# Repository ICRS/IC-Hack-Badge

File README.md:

# IC-Hack-Badge

Repository for how to use and program the IC Hack PCB badges. They are functionally very similar to the [Raspberry Pi Pico](https://www.raspberrypi.com/products/raspberry-pi-pico/), and any guides for that board will likely work for this one too.

Microcontrollers are small but flexible computers that are great at interacting with the real world. We hope that by giving everyone a powerful microcontroller like the RP2040, they are able to give embedded programming a go and make something cool!

Kits of sensors and electronics are available from ICRS to help build whatever you have in mind. ICRS can also provide knowledge and help with anything relating to hardware projects and the badges.

The badges were designed using [KiCad](https://www.kicad.org/) and all the design files and schematics are available in the [/Hardware](/Hardware/) folder.

## Contents

- [Features](#features)
- [Pinout](#pinout)
- [Writing Code](#writing-code)
- [Uploading Code & Boot Mode](#uploading-code--boot-mode)
- [Resetting Your Badge](#resetting-your-badge)
- [Running From Battery](#running-from-battery)
- [Credits](#credits)

## Features

The features of the board are listed below:

- RP2040: Dual Arm Cortex M0+ cores up to 133MHz
- 264kB RAM
- 2MB Flash
- 24*5 Pixel LED Matrix
- Light up LED logo
- CR2450 Battery holder
- USB C

## Pinout

The functions of each pin are shown here from the back side.

These pins can be connected to using standard Dupont 2.54mm jumper cables.

There are also pins that connect to things internally on the board:

| **Pin Number** | **Function**         |
|----------------|----------------------|
| 0              | Button Y             |
| 1              | Button B             |
| 2              | Button X             |
| 3              | Button A             |
| 4              | Logo H               |
| 5              | Logo C               |
| 6              | Logo I               |
| 15             | Display serial data  |
| 16             | Display enable       |
| 17             | Display serial clock |
| 18             | Display latch        |

## Writing Code

There are several ways of programming the board using either C/C++ or MicroPython.

- [Arduino](#arduino)
- [MicroPython](#micropython)
- [VS Code & C/C++ SDK](#vs-code--cc-sdk)

### Arduino

Arduino is an open source platform for programming microcontrollers in C++. An [Arduino library](https://github.com/ICRS/IC-Hack-Badge-Arduino) has been written for the board that makes using the built in LED matrix easy.

To get started, [download Arduino](https://www.arduino.cc/en/software).

Once you have it running go to `file > preferences` and add the following link to `Additional boards manager URLs`: https://github.com/earlephilhower/arduino-pico/releases/download/global/package_rp2040_index.json

You then need to install support for the RP2040 by going to the board manager tab on the left, searching for "Raspberry Pi Pico" and installing the one by Earle F. Philhower, III.

Go to the board selector in the top, and set the current board to the `Raspberry Pi Pico`.

Finally, we need to install the library made for this board by going to the library manager tab on the left, searching for IC Hack Badge, and installing the most recent version. 

You can then check out example code in `File > Examples > IC Hack Badge`, or start writing your own code.

To program the badge, put the board in [boot mode](#uploading-code--boot-mode) and select the port it is connected to through the same menu where you chose the current board. You may need to check the `Show all ports` box. Then press the upload arrow in the top left.

### MicroPython

To use MicroPython first upload the interpreter to the badge using the [latest firmware from Raspberry Pi](https://micropython.org/download/rp2-pico/rp2-pico-latest.uf2), which you can upload using the instructions in [Uploading Code & Boot Mode](#uploading-code--boot-mode).

You can then connect to the serial port using a program such as PuTTY on Windows, or Minicom on Linux, and start executing code in the MicroPython shell.

Here we are printing "Hello World" over USB, and then setting pin 4 high, which turns on the H LEDs on the badge's logo. The mapping of pins to their functions is shown in the [Pinout](#pinout) section.

You can use the [MicroPico](https://marketplace.visualstudio.com/items?itemName=paulober.pico-w-go) VS Code extension, or [Thonny](https://thonny.org/) to write programs that you can then upload to the badge.

See the [documentation by Raspberry Pi](https://www.raspberrypi.com/documentation/microcontrollers/micropython.html) for more info and APIs.

Currently there is no MicroPython code for writing to the LED matrix, but both the Arduino library and the default firmware have implementations in C++ that could be ported to Python.

### VS Code & C/C++ SDK

The C/C++ SDK is the official way released by Raspberry Pi for programming the RP2040 microcontroller. It offers more depth and features than Arduino, but lacks Arduino's abstractions and libraries, that can make using it harder.

Setting it up can be a bit more challenging than using Arduino too (especially on Windows), and we recommend following [Raspberry Pi's guides](https://www.raspberrypi.com/documentation/microcontrollers/c_sdk.html) if you want to do so.

The firmware flashed to all the badges was written using the C/C++ SDK, and can be found in the [/SDK](/SDK/) folder for reference. Sorry for the spaghetti, blame Haotian -_-

## Uploading Code & Boot Mode

Plug the board into a computer using the USB C connector. Then in order to program the board it needs to be put into "boot mode". This is done by **holding down** both the reset button (**RST**) on the top of the board **and** the boot button (**BOOT**) on the bottom of the board. Then **release RST**, wait a bit and **release BOOT**.

This will make the board show up as a USB drive that you can drag and drop compiled uf2 binaries into.

## Resetting Your Badge
The default firmware is [firmware.uf2](/firmware.uf2) and you can upload it to your badge with a USB C cable after putting it in [boot mode](#uploading-code--boot-mode).

## Running From Battery

Coin cells are able to supply a maximum of around 10mA continuously (ideally <2mA), but the RP2040 when running at full speed can draw well over 20mA. This means that the power consumption needs to be lowered by changing the CPU frequency and voltage so it can be run on the battery.

This can be done in C/C++ using the following lines:

```C
#include "pico/stdlib.h"
#include "hardware/vreg.h"

void main() {
  vreg_set_voltage(VREG_VOLTAGE_0_90);
  set_sys_clock_khz(18000, false);
  ...
}
```

This lowers the core voltage to 0.9V, and the core frequency to 18MHz which draws around 6mA. This was found to be a good balance of low power and stablility, however it means the USB is disabled since it requires a minimum of 48MHz.

> [!NOTE]
> The battery should last for well over 24 hours with the default firmware, so it can be left on for the whole hackathon.

Using the pico extras repo in the C/C++ SDK (sadly not in Arduino) the chip can be put to sleep which only draws 0.7mA. You can find out more about pico_sleep [here](https://github.com/raspberrypi/pico-extras/tree/master).

When running MicroPython the RP2040 consumes too much power for the battery, so you should use USB instead.

## Credits

Hardware: Ben Smith

Artwork: Anna Votin and Kevin Wang

Firmware: Haotian Wu (+ Ben Smith)

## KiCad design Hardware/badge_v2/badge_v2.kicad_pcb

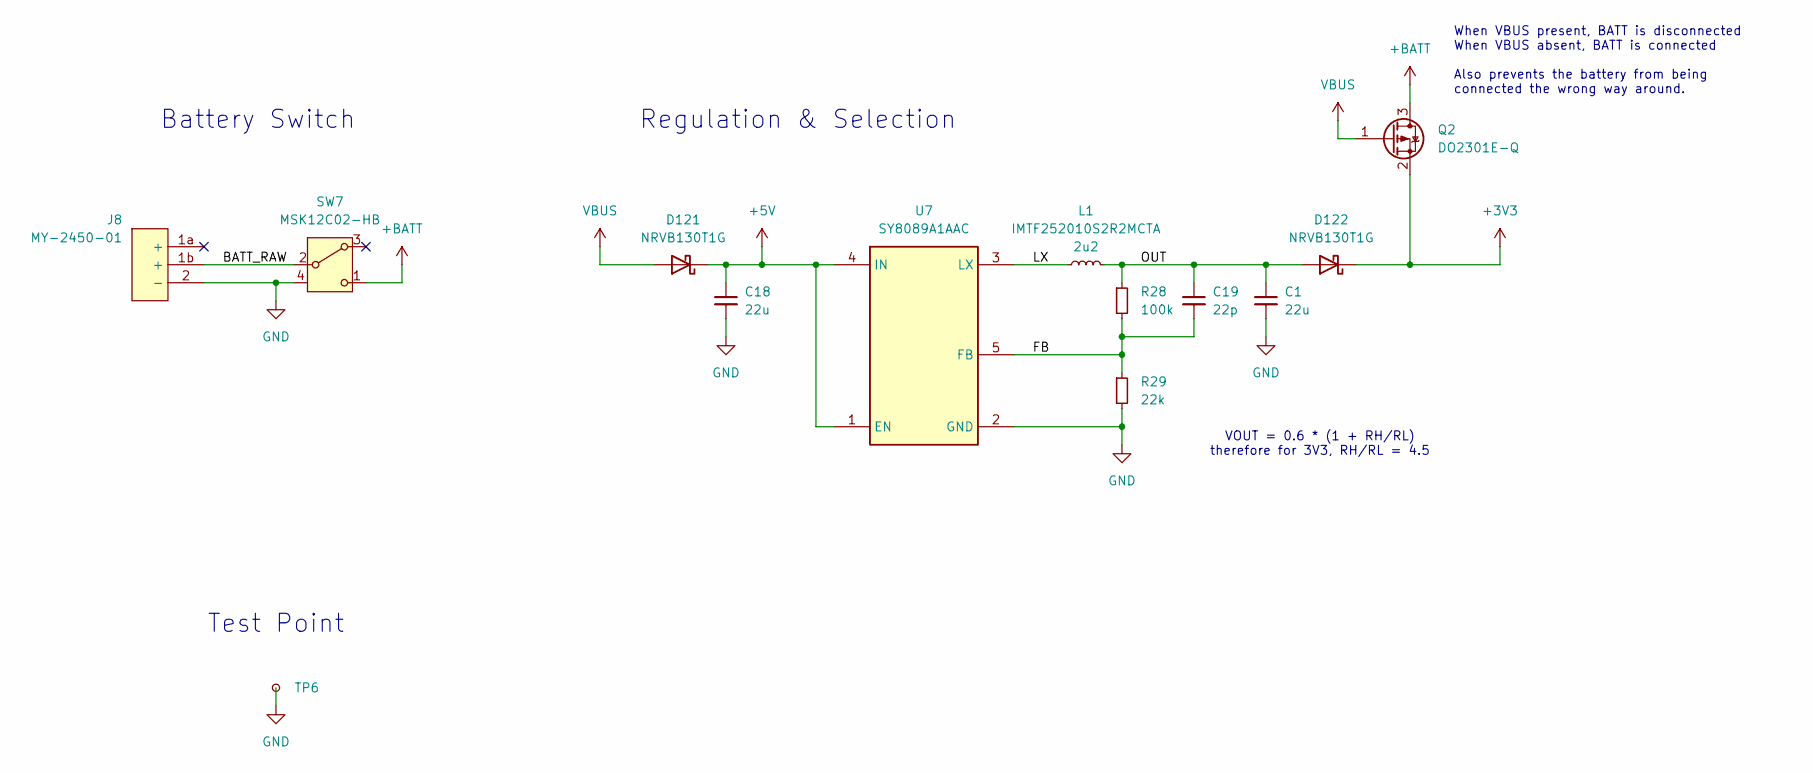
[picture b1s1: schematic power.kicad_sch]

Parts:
C1, C18: 22u; C_0603_1608Metric
C19: 22p; C_0402_1005Metric
D121, D122: NRVB130T1G; D_SOD-123F; LCSC part number C917121
J8: MY-2450-01; LCSC part number C964845
L1: 2u2; L_1008_2520Metric; Part IMTF252010S2R2MCTA; LCSC part number C19631588
Q2: DO2301E-Q; SOT-23; LCSC part number C41384537
R28: 100k; R_0402_1005Metric
R29: 22k; R_0402_1005Metric
SW7: MSK12C02-HB; LCSC part number C5149817
TP6: TestPoint_Small; TestPoint_Pad_D3.0mm
U7: SY8089A1AAC; SOT95P285X130-5N; Manufacturer_Part_Number SY8089A1AAC; LCSC part number C479074

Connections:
+3V3: D122.1 (K), Q2.2 (S); also elsewhere on the board
+5V: C18.1, D121.1 (K), U7.1 (EN), U7.4 (IN); also elsewhere on the board
+BATT: Q2.3 (D), SW7.1 (C)
/Power/BATT_RAW: J8.1b (+), SW7.2 (B)
/Power/FB: C19.2, R28.2, R29.1, U7.5 (FB)
/Power/LX: L1.1, U7.3 (LX)
/Power/OUT: C1.1, C19.1, D122.2 (A), L1.2, R28.1
GND: C1.2, C18.2, J8.2 (-), R29.2, SW7.4, TP6.1, U7.2 (GND); also elsewhere on the board
VBUS: D121.2 (A), Q2.1 (G); also elsewhere on the board

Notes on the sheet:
Battery Switch
Test Point
When VBUS present, BATT is disconnected When VBUS absent, BATT is connected Also prevents the battery from being connected the wrong way around.
Regulation & Selection
VOUT = 0.6 * (1 + RH/RL) therefore for 3V3, RH/RL = 4.5

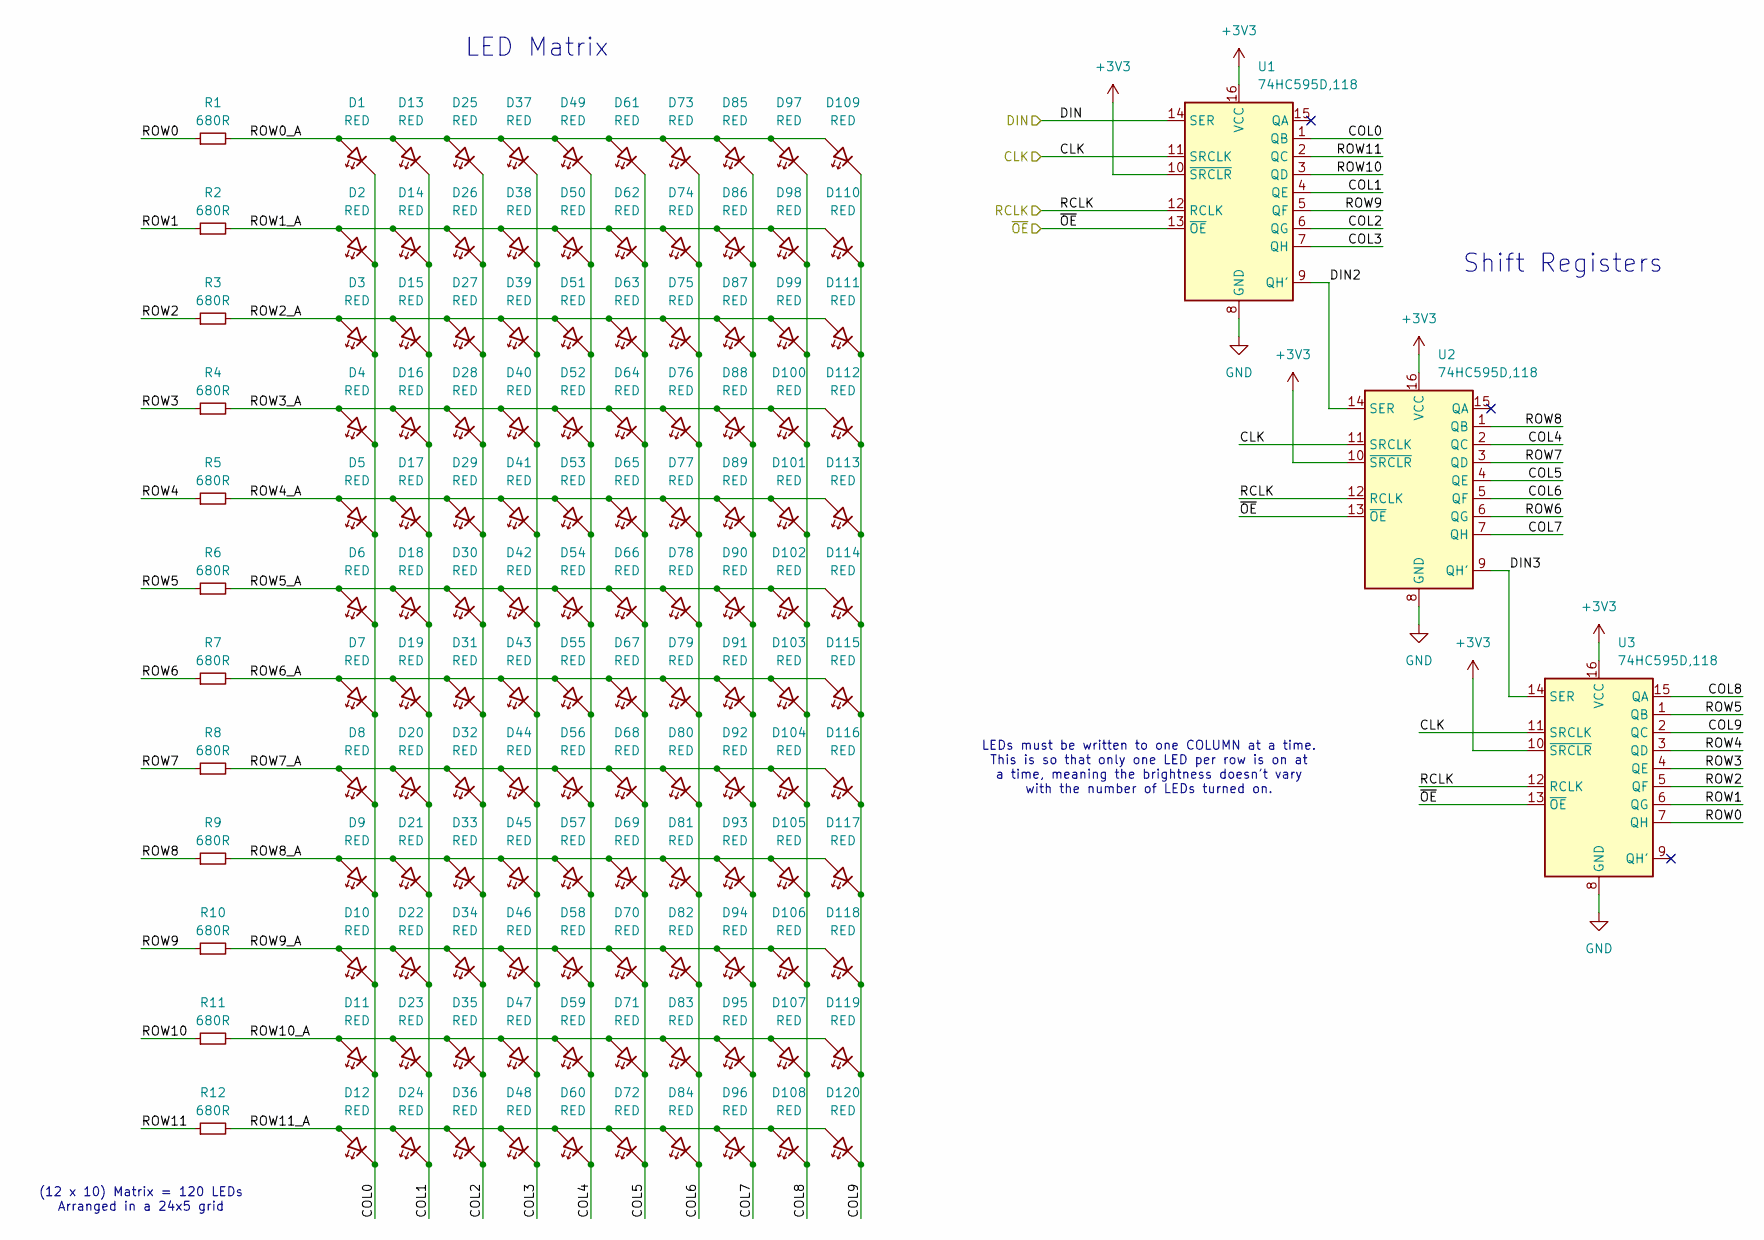
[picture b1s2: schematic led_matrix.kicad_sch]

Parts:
D1, D2, D3, D4, D5, D6, D7, D8, D9, D10, D11, D12, D13, D14, D15, D16, D17, D18, D19, D20, D21, D22, D23, D24, D25, D26, D27, D28, D29, D30, D31, D32, D33, D34, D35, D36, D37, D38, D39, D40, D41, D42, D43, D44, D45, D46, D47, D48, D49, D50, D51, D52, D53, D54, D55, D56, D57, D58, D59, D60, D61, D62, D63, D64, D65, D66, D67, D68, D69, D70, D71, D72, D73, D74, D75, D76, D77, D78, D79, D80, D81, D82, D83, D84, D85, D86, D87, D88, D89, D90, D91, D92, D93, D94, D95, D96, D97, D98, D99, D100, D101, D102, D103, D104, D105, D106, D107, D108, D109, D110, D111, D112, D113, D114, D115, D116, D117, D118, D119, D120: RED; LED_0402_1005Metric
R1, R2, R3, R4, R5, R6, R7, R8, R9, R10, R11, R12: 680R; R_0402_1005Metric
U1, U2, U3: 74HC595D,118; SOIC-16_3.9x9.9mm_P1.27mm; LCSC part number C5947

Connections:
+3V3: U1.10 (~SRCLR), U1.16 (VCC), U2.10 (~SRCLR), U2.16 (VCC), U3.10 (~SRCLR), U3.16 (VCC); also elsewhere on the board
/LED Matrix/CLK: U1.11 (SRCLK), U2.11 (SRCLK), U3.11 (SRCLK); also elsewhere on the board
/LED Matrix/COL0: D1.1 (K), D2.1 (K), D3.1 (K), D4.1 (K), D5.1 (K), D6.1 (K), D7.1 (K), D8.1 (K), D9.1 (K), D10.1 (K), D11.1 (K), D12.1 (K), U1.1 (QB)
/LED Matrix/COL1: D13.1 (K), D14.1 (K), D15.1 (K), D16.1 (K), D17.1 (K), D18.1 (K), D19.1 (K), D20.1 (K), D21.1 (K), D22.1 (K), D23.1 (K), D24.1 (K), U1.4 (QE)
/LED Matrix/COL2: D25.1 (K), D26.1 (K), D27.1 (K), D28.1 (K), D29.1 (K), D30.1 (K), D31.1 (K), D32.1 (K), D33.1 (K), D34.1 (K), D35.1 (K), D36.1 (K), U1.6 (QG)
/LED Matrix/COL3: D37.1 (K), D38.1 (K), D39.1 (K), D40.1 (K), D41.1 (K), D42.1 (K), D43.1 (K), D44.1 (K), D45.1 (K), D46.1 (K), D47.1 (K), D48.1 (K), U1.7 (QH)
/LED Matrix/COL4: D49.1 (K), D50.1 (K), D51.1 (K), D52.1 (K), D53.1 (K), D54.1 (K), D55.1 (K), D56.1 (K), D57.1 (K), D58.1 (K), D59.1 (K), D60.1 (K), U2.2 (QC)
/LED Matrix/COL5: D61.1 (K), D62.1 (K), D63.1 (K), D64.1 (K), D65.1 (K), D66.1 (K), D67.1 (K), D68.1 (K), D69.1 (K), D70.1 (K), D71.1 (K), D72.1 (K), U2.4 (QE)
/LED Matrix/COL6: D73.1 (K), D74.1 (K), D75.1 (K), D76.1 (K), D77.1 (K), D78.1 (K), D79.1 (K), D80.1 (K), D81.1 (K), D82.1 (K), D83.1 (K), D84.1 (K), U2.5 (QF)
/LED Matrix/COL7: D85.1 (K), D86.1 (K), D87.1 (K), D88.1 (K), D89.1 (K), D90.1 (K), D91.1 (K), D92.1 (K), D93.1 (K), D94.1 (K), D95.1 (K), D96.1 (K), U2.7 (QH)
/LED Matrix/COL8: D97.1 (K), D98.1 (K), D99.1 (K), D100.1 (K), D101.1 (K), D102.1 (K), D103.1 (K), D104.1 (K), D105.1 (K), D106.1 (K), D107.1 (K), D108.1 (K), U3.15 (QA)
/LED Matrix/COL9: D109.1 (K), D110.1 (K), D111.1 (K), D112.1 (K), D113.1 (K), D114.1 (K), D115.1 (K), D116.1 (K), D117.1 (K), D118.1 (K), D119.1 (K), D120.1 (K), U3.2 (QC)
/LED Matrix/DIN: U1.14 (SER); also elsewhere on the board
/LED Matrix/DIN2: U1.9 (QH'), U2.14 (SER)
/LED Matrix/DIN3: U2.9 (QH'), U3.14 (SER)
/LED Matrix/RCLK: U1.12 (RCLK), U2.12 (RCLK), U3.12 (RCLK); also elsewhere on the board
/LED Matrix/ROW0: R1.1, U3.7 (QH)
/LED Matrix/ROW0_A: D1.2 (A), D13.2 (A), D25.2 (A), D37.2 (A), D49.2 (A), D61.2 (A), D73.2 (A), D85.2 (A), D97.2 (A), D109.2 (A), R1.2
/LED Matrix/ROW1: R2.1, U3.6 (QG)
/LED Matrix/ROW1_A: D2.2 (A), D14.2 (A), D26.2 (A), D38.2 (A), D50.2 (A), D62.2 (A), D74.2 (A), D86.2 (A), D98.2 (A), D110.2 (A), R2.2
/LED Matrix/ROW2: R3.1, U3.5 (QF)
/LED Matrix/ROW2_A: D3.2 (A), D15.2 (A), D27.2 (A), D39.2 (A), D51.2 (A), D63.2 (A), D75.2 (A), D87.2 (A), D99.2 (A), D111.2 (A), R3.2
/LED Matrix/ROW3: R4.1, U3.4 (QE)
/LED Matrix/ROW3_A: D4.2 (A), D16.2 (A), D28.2 (A), D40.2 (A), D52.2 (A), D64.2 (A), D76.2 (A), D88.2 (A), D100.2 (A), D112.2 (A), R4.2
/LED Matrix/ROW4: R5.1, U3.3 (QD)
/LED Matrix/ROW4_A: D5.2 (A), D17.2 (A), D29.2 (A), D41.2 (A), D53.2 (A), D65.2 (A), D77.2 (A), D89.2 (A), D101.2 (A), D113.2 (A), R5.2
/LED Matrix/ROW5: R6.1, U3.1 (QB)
/LED Matrix/ROW5_A: D6.2 (A), D18.2 (A), D30.2 (A), D42.2 (A), D54.2 (A), D66.2 (A), D78.2 (A), D90.2 (A), D102.2 (A), D114.2 (A), R6.2
/LED Matrix/ROW6: R7.1, U2.6 (QG)
/LED Matrix/ROW6_A: D7.2 (A), D19.2 (A), D31.2 (A), D43.2 (A), D55.2 (A), D67.2 (A), D79.2 (A), D91.2 (A), D103.2 (A), D115.2 (A), R7.2
/LED Matrix/ROW7: R8.1, U2.3 (QD)
/LED Matrix/ROW7_A: D8.2 (A), D20.2 (A), D32.2 (A), D44.2 (A), D56.2 (A), D68.2 (A), D80.2 (A), D92.2 (A), D104.2 (A), D116.2 (A), R8.2
/LED Matrix/ROW8: R9.1, U2.1 (QB)
/LED Matrix/ROW8_A: D9.2 (A), D21.2 (A), D33.2 (A), D45.2 (A), D57.2 (A), D69.2 (A), D81.2 (A), D93.2 (A), D105.2 (A), D117.2 (A), R9.2
/LED Matrix/ROW9: R10.1, U1.5 (QF)
/LED Matrix/ROW9_A: D10.2 (A), D22.2 (A), D34.2 (A), D46.2 (A), D58.2 (A), D70.2 (A), D82.2 (A), D94.2 (A), D106.2 (A), D118.2 (A), R10.2
/LED Matrix/ROW10: R11.1, U1.3 (QD)
/LED Matrix/ROW10_A: D11.2 (A), D23.2 (A), D35.2 (A), D47.2 (A), D59.2 (A), D71.2 (A), D83.2 (A), D95.2 (A), D107.2 (A), D119.2 (A), R11.2
/LED Matrix/ROW11: R12.1, U1.2 (QC)
/LED Matrix/ROW11_A: D12.2 (A), D24.2 (A), D36.2 (A), D48.2 (A), D60.2 (A), D72.2 (A), D84.2 (A), D96.2 (A), D108.2 (A), D120.2 (A), R12.2
/LED Matrix/~OE: U1.13 (~OE), U2.13 (~OE), U3.13 (~OE); also elsewhere on the board
GND: U1.8 (GND), U2.8 (GND), U3.8 (GND); also elsewhere on the board

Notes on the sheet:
LEDs must be written to one COLUMN at a time. This is so that only one LED per row is on at a time, meaning the brightness doesn't vary with the number of LEDs turned on.
LED Matrix
Shift Registers
(12 x 10) Matrix = 120 LEDs Arranged in a 24x5 grid

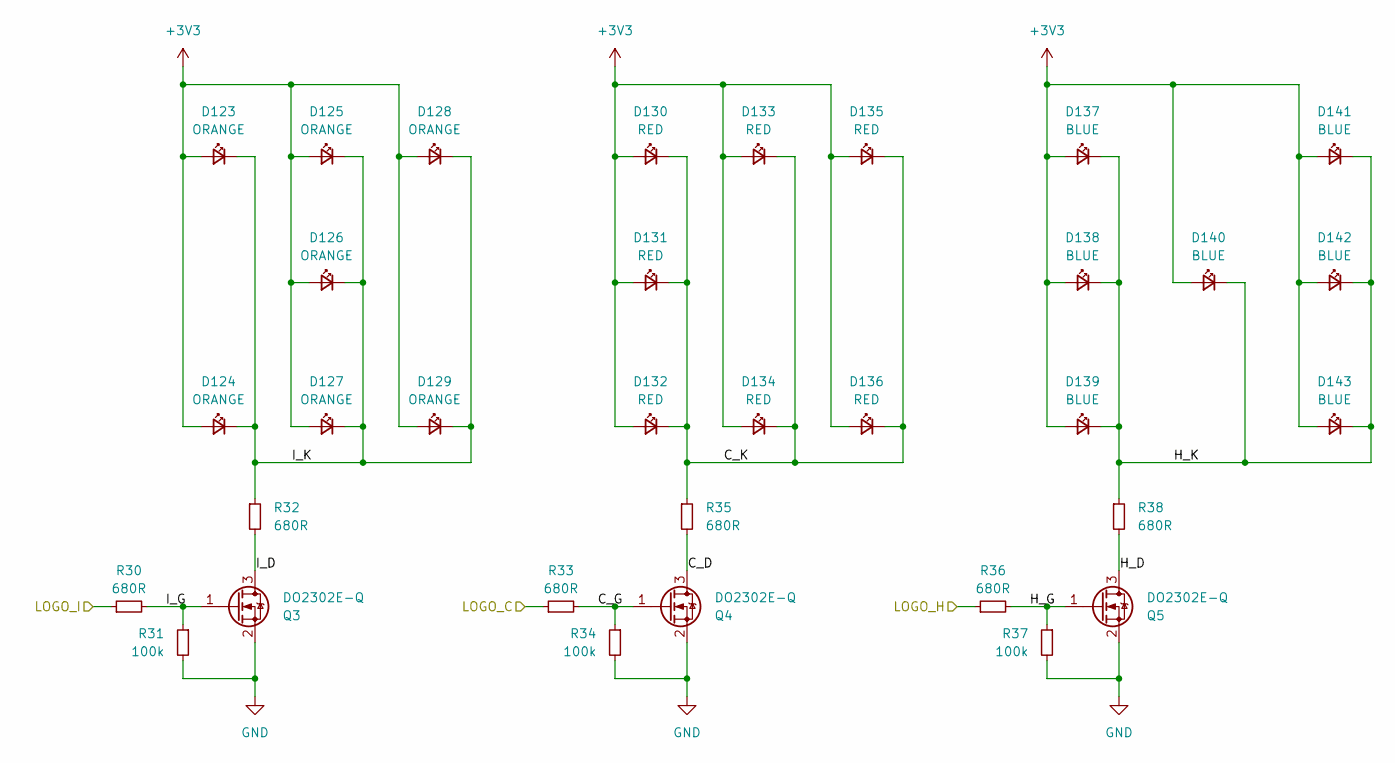
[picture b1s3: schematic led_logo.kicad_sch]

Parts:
D123, D124, D125, D126, D127, D128, D129: ORANGE; LED_0402_1005Metric
D130, D131, D132, D133, D134, D135, D136: RED; LED_0402_1005Metric
D137, D138, D139, D140, D141, D142, D143: BLUE; LED_0402_1005Metric
Q3, Q4, Q5: DO2302E-Q; SOT-23; LCSC part number C41384540
R30, R32, R33, R35, R36, R38: 680R; R_0402_1005Metric
R31, R34, R37: 100k; R_0402_1005Metric

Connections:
+3V3: D123.2 (A), D124.2 (A), D125.2 (A), D126.2 (A), D127.2 (A), D128.2 (A), D129.2 (A), D130.2 (A), D131.2 (A), D132.2 (A), D133.2 (A), D134.2 (A), D135.2 (A), D136.2 (A), D137.2 (A), D138.2 (A), D139.2 (A), D140.2 (A), D141.2 (A), D142.2 (A), D143.2 (A); also elsewhere on the board
/LED Logo/C_D: Q4.3 (D), R35.2
/LED Logo/C_G: Q4.1 (G), R33.2, R34.1
/LED Logo/C_K: D130.1 (K), D131.1 (K), D132.1 (K), D133.1 (K), D134.1 (K), D135.1 (K), D136.1 (K), R35.1
/LED Logo/H_D: Q5.3 (D), R38.2
/LED Logo/H_G: Q5.1 (G), R36.2, R37.1
/LED Logo/H_K: D137.1 (K), D138.1 (K), D139.1 (K), D140.1 (K), D141.1 (K), D142.1 (K), D143.1 (K), R38.1
/LED Logo/I_D: Q3.3 (D), R32.2
/LED Logo/I_G: Q3.1 (G), R30.2, R31.1
/LED Logo/I_K: D123.1 (K), D124.1 (K), D125.1 (K), D126.1 (K), D127.1 (K), D128.1 (K), D129.1 (K), R32.1
/LED Logo/LOGO_C: R33.1; also elsewhere on the board
/LED Logo/LOGO_H: R36.1; also elsewhere on the board
/LED Logo/LOGO_I: R30.1; also elsewhere on the board
GND: Q3.2 (S), Q4.2 (S), Q5.2 (S), R31.2, R34.2, R37.2; also elsewhere on the board

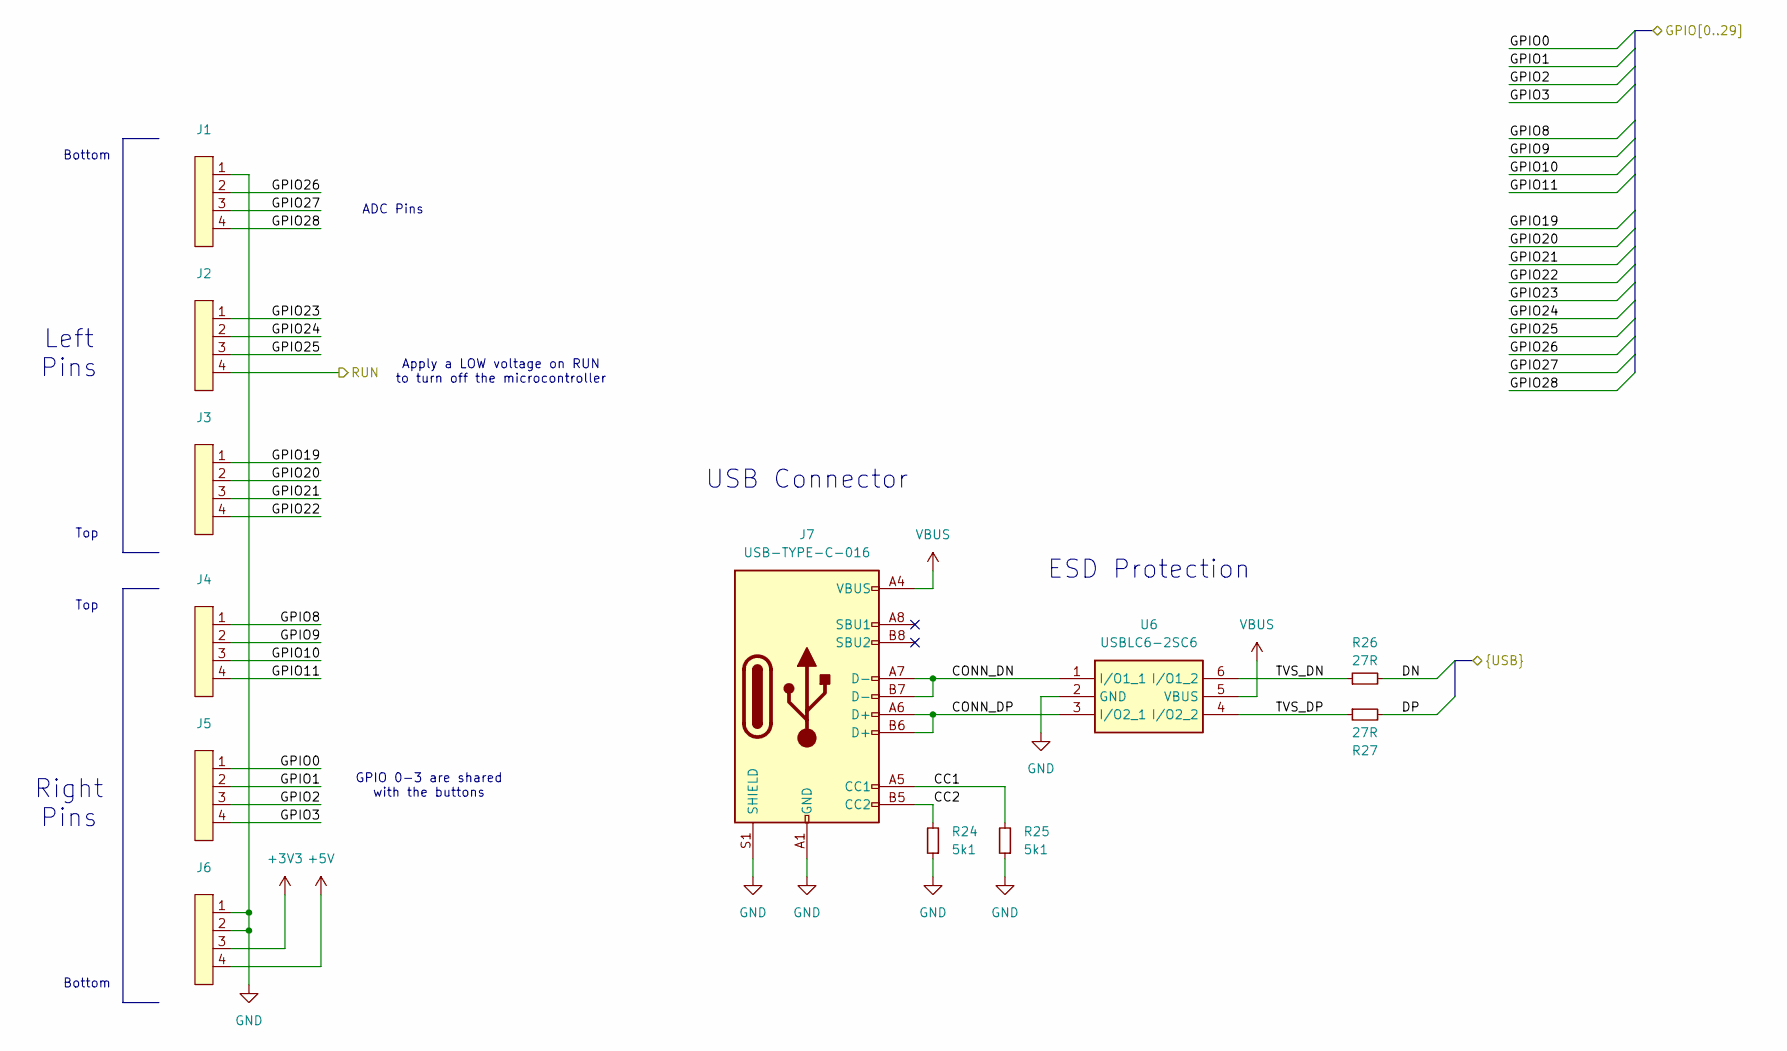
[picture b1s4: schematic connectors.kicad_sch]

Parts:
J1, J2, J3, J4, J5, J6: X6511FRS-04-C85D30; LCSC part number C5142237
J7: USB-TYPE-C-016; LCSC part number C2927036
R24, R25: 5k1; R_0402_1005Metric
R26, R27: 27R; R_0402_1005Metric
U6: USBLC6-2SC6; SOT95P280X145-6N; Manufacturer_Part_Number USBLC6-2SC6; Mouser Part Number 511-USBLC6-2SC6

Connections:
+3V3: J6.3; also elsewhere on the board
+5V: J6.4; also elsewhere on the board
/Connectors/CC1: J7.A5 (CC1), R25.2
/Connectors/CC2: J7.B5 (CC2), R24.2
/Connectors/CONN_DN: J7.A7 (D-), J7.B7 (D-), U6.1 (I/O1_1)
/Connectors/CONN_DP: J7.A6 (D+), J7.B6 (D+), U6.3 (I/O2_1)
/Connectors/DN: R26.2; also elsewhere on the board
/Connectors/DP: R27.2; also elsewhere on the board
/Connectors/GPIO0: J5.1; also elsewhere on the board
/Connectors/GPIO1: J5.2; also elsewhere on the board
/Connectors/GPIO2: J5.3; also elsewhere on the board
/Connectors/GPIO3: J5.4; also elsewhere on the board
/Connectors/GPIO8: J4.1; also elsewhere on the board
/Connectors/GPIO9: J4.2; also elsewhere on the board
/Connectors/GPIO10: J4.3; also elsewhere on the board
/Connectors/GPIO11: J4.4; also elsewhere on the board
/Connectors/GPIO19: J3.1; also elsewhere on the board
/Connectors/GPIO20: J3.2; also elsewhere on the board
/Connectors/GPIO21: J3.3; also elsewhere on the board
/Connectors/GPIO22: J3.4; also elsewhere on the board
/Connectors/GPIO23: J2.1; also elsewhere on the board
/Connectors/GPIO24: J2.2; also elsewhere on the board
/Connectors/GPIO25: J2.3; also elsewhere on the board
/Connectors/GPIO26: J1.2; also elsewhere on the board
/Connectors/GPIO27: J1.3; also elsewhere on the board
/Connectors/GPIO28: J1.4; also elsewhere on the board
/Connectors/TVS_DN: R26.1, U6.6 (I/O1_2)
/Connectors/TVS_DP: R27.1, U6.4 (I/O2_2)
/RP2040/RUN: J2.4; also elsewhere on the board
GND: J1.1, J6.1, J6.2, J7.A1 (GND), J7.A12 (GND), J7.B1 (GND), J7.B12 (GND), J7.S1 (SHIELD), R24.1, R25.1, U6.2 (GND); also elsewhere on the board
VBUS: J7.A4 (VBUS), J7.A9 (VBUS), J7.B4 (VBUS), J7.B9 (VBUS), U6.5 (VBUS); also elsewhere on the board

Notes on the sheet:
ESD Protection
ADC Pins
Top
GPIO 0-3 are shared with the buttons
Left Pins
Apply a LOW voltage on RUN to turn off the microcontroller
USB Connector
Bottom
Right Pins

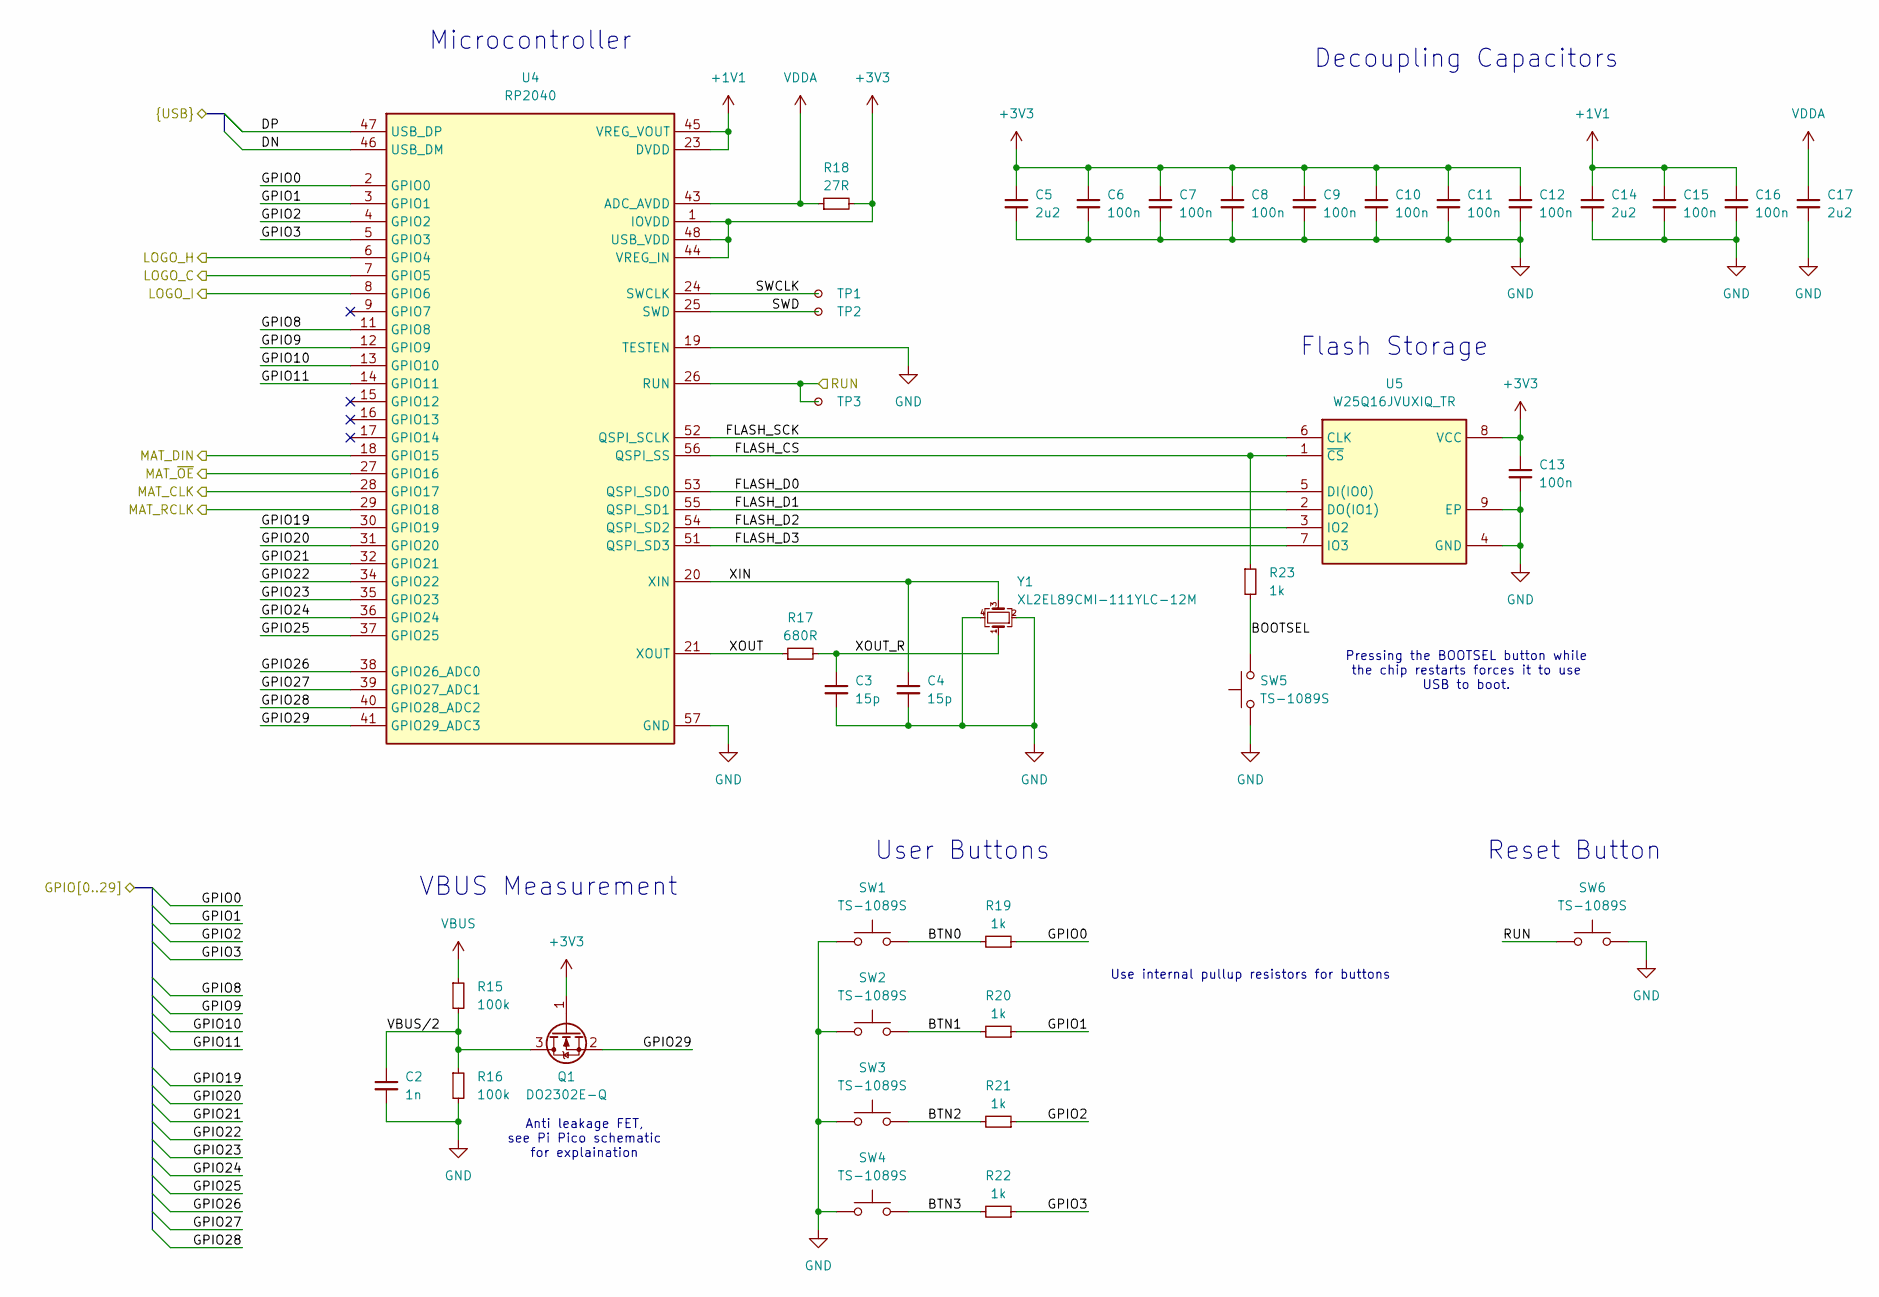
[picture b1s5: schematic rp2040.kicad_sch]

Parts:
C2: 1n; C_0402_1005Metric
C3, C4: 15p; C_0402_1005Metric
C5, C14, C17: 2u2; C_0402_1005Metric
C6, C7, C8, C9, C10, C11, C12, C13, C15, C16: 100n; C_0402_1005Metric
Q1: DO2302E-Q; SOT-23; LCSC part number C41384540
R15, R16: 100k; R_0402_1005Metric
R17: 680R; R_0402_1005Metric
R18: 27R; R_0402_1005Metric
R19, R20, R21, R22, R23: 1k; R_0402_1005Metric
SW1, SW2, SW3, SW4, SW5, SW6: TS-1089S; LCSC part number C455282
TP1, TP2, TP3: TestPoint_Small; TestPoint_Pad_D3.0mm
U4: RP2040; QFN-56-1EP_7x7mm_P0.4mm_EP3.2x3.2mm; LCSC part number C2040
U5: W25Q16JVUXIQ_TR; SON50P300X200X60-9N; Manufacturer_Part_Number W25Q16JVUXIQ TR; Mouser Part Number 454-W25Q16JVUXIQTR
Y1: XL2EL89CMI-111YLC-12M; Crystal_SMD_3225-4Pin_3.2x2.5mm; LCSC part number C7500570

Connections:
+1V1: C14.1, C15.1, C16.1, U4.23 (DVDD), U4.45 (VREG_VOUT), U4.50 (DVDD)
+3V3: C5.1, C6.1, C7.1, C8.1, C9.1, C10.1, C11.1, C12.1, C13.1, Q1.1 (G), R18.2, U4.1 (IOVDD), U4.10 (IOVDD), U4.22 (IOVDD), U4.33 (IOVDD), U4.42 (IOVDD), U4.44 (VREG_IN), U4.48 (USB_VDD), U4.49 (IOVDD), U5.8 (VCC); also elsewhere on the board
/Connectors/DN: U4.46 (USB_DM); also elsewhere on the board
/Connectors/DP: U4.47 (USB_DP); also elsewhere on the board
/Connectors/GPIO0: R19.1, U4.2 (GPIO0); also elsewhere on the board
/Connectors/GPIO1: R20.1, U4.3 (GPIO1); also elsewhere on the board
/Connectors/GPIO2: R21.1, U4.4 (GPIO2); also elsewhere on the board
/Connectors/GPIO3: R22.1, U4.5 (GPIO3); also elsewhere on the board
/Connectors/GPIO8: U4.11 (GPIO8); also elsewhere on the board
/Connectors/GPIO9: U4.12 (GPIO9); also elsewhere on the board
/Connectors/GPIO10: U4.13 (GPIO10); also elsewhere on the board
/Connectors/GPIO11: U4.14 (GPIO11); also elsewhere on the board
/Connectors/GPIO19: U4.30 (GPIO19); also elsewhere on the board
/Connectors/GPIO20: U4.31 (GPIO20); also elsewhere on the board
/Connectors/GPIO21: U4.32 (GPIO21); also elsewhere on the board
/Connectors/GPIO22: U4.34 (GPIO22); also elsewhere on the board
/Connectors/GPIO23: U4.35 (GPIO23); also elsewhere on the board
/Connectors/GPIO24: U4.36 (GPIO24); also elsewhere on the board
/Connectors/GPIO25: U4.37 (GPIO25); also elsewhere on the board
/Connectors/GPIO26: U4.38 (GPIO26_ADC0); also elsewhere on the board
/Connectors/GPIO27: U4.39 (GPIO27_ADC1); also elsewhere on the board
/Connectors/GPIO28: U4.40 (GPIO28_ADC2); also elsewhere on the board
/Connectors/GPIO29: Q1.2 (S), U4.41 (GPIO29_ADC3)
/LED Logo/LOGO_C: U4.7 (GPIO5); also elsewhere on the board
/LED Logo/LOGO_H: U4.6 (GPIO4); also elsewhere on the board
/LED Logo/LOGO_I: U4.8 (GPIO6); also elsewhere on the board
/LED Matrix/CLK: U4.28 (GPIO17); also elsewhere on the board
/LED Matrix/DIN: U4.18 (GPIO15); also elsewhere on the board
/LED Matrix/RCLK: U4.29 (GPIO18); also elsewhere on the board
/LED Matrix/~OE: U4.27 (GPIO16); also elsewhere on the board
/RP2040/BOOTSEL: R23.2, SW5.2
/RP2040/BTN0: R19.2, SW1.1
/RP2040/BTN1: R20.2, SW2.1
/RP2040/BTN2: R21.2, SW3.1
/RP2040/BTN3: R22.2, SW4.1
/RP2040/FLASH_CS: R23.1, U4.56 (QSPI_SS), U5.1 (~CS)
/RP2040/FLASH_D0: U4.53 (QSPI_SD0), U5.5 (DI(IO0))
/RP2040/FLASH_D1: U4.55 (QSPI_SD1), U5.2 (DO(IO1))
/RP2040/FLASH_D2: U4.54 (QSPI_SD2), U5.3 (IO2)
/RP2040/FLASH_D3: U4.51 (QSPI_SD3), U5.7 (IO3)
/RP2040/FLASH_SCK: U4.52 (QSPI_SCLK), U5.6 (CLK)
/RP2040/RUN: SW6.1, TP3.1, U4.26 (RUN); also elsewhere on the board
/RP2040/SWCLK: TP1.1, U4.24 (SWCLK)
/RP2040/SWD: TP2.1, U4.25 (SWD)
/RP2040/VBUS/2: C2.1, Q1.3 (D), R15.2, R16.1
/RP2040/XIN: C4.1, U4.20 (XIN), Y1.3
/RP2040/XOUT: R17.1, U4.21 (XOUT)
/RP2040/XOUT_R: C3.1, R17.2, Y1.1
GND: C2.2, C3.2, C4.2, C5.2, C6.2, C7.2, C8.2, C9.2, C10.2, C11.2, C12.2, C13.2, C14.2, C15.2, C16.2, C17.2, R16.2, SW1.2, SW2.2, SW3.2, SW4.2, SW5.1, SW6.2, U4.19 (TESTEN), U4.57 (GND), U5.4 (GND), U5.9 (EP), Y1.2, Y1.4; also elsewhere on the board
VBUS: R15.1; also elsewhere on the board
VDDA: C17.1, R18.1, U4.43 (ADC_AVDD)

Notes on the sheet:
Decoupling Capacitors
Use internal pullup resistors for buttons
Flash Storage
Microcontroller
User Buttons
VBUS Measurement
Reset Button
Anti leakage FET, see Pi Pico schematic for explaination
Pressing the BOOTSEL button while the chip restarts forces it to use USB to boot.

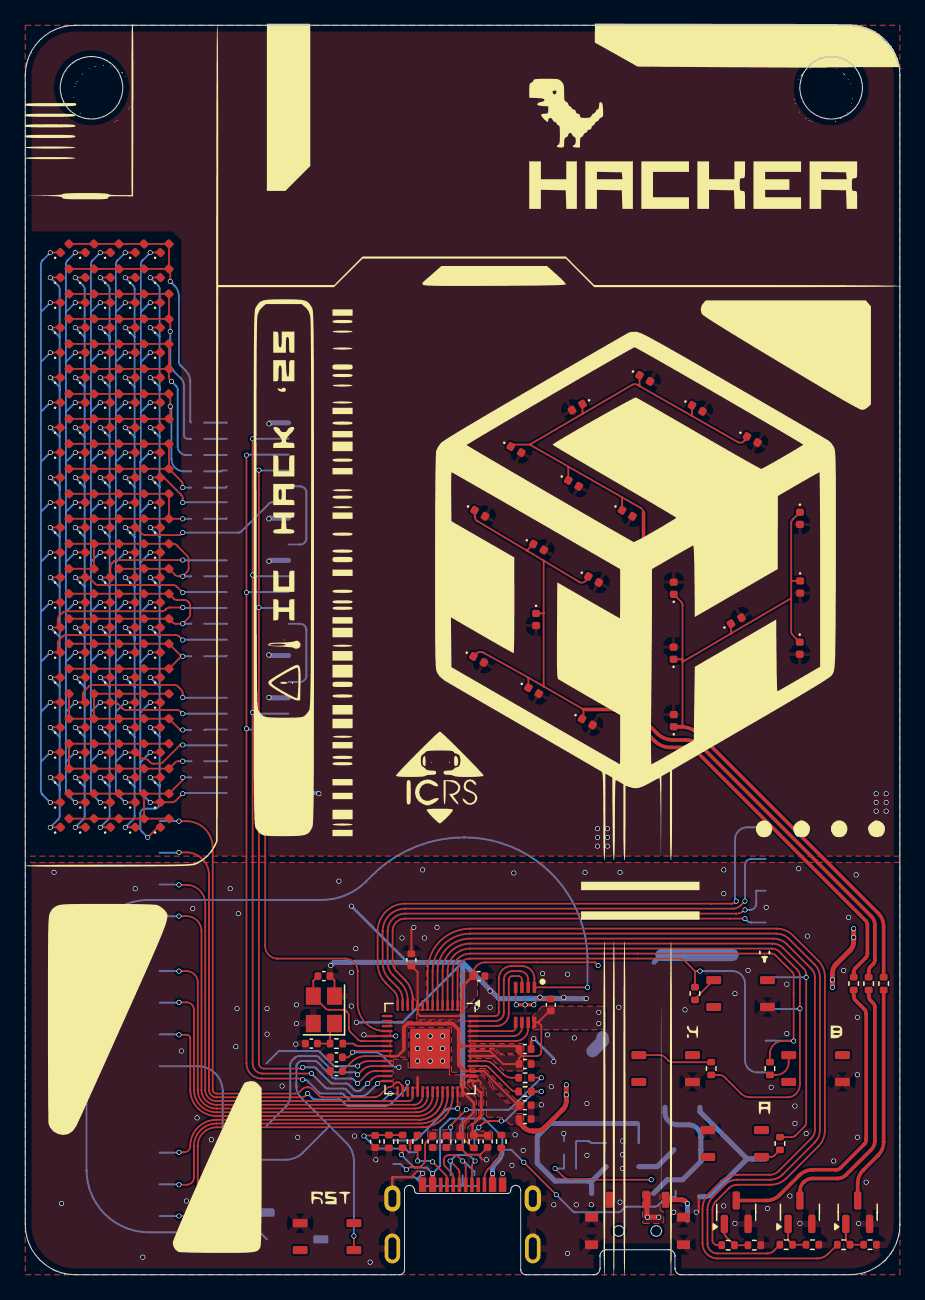
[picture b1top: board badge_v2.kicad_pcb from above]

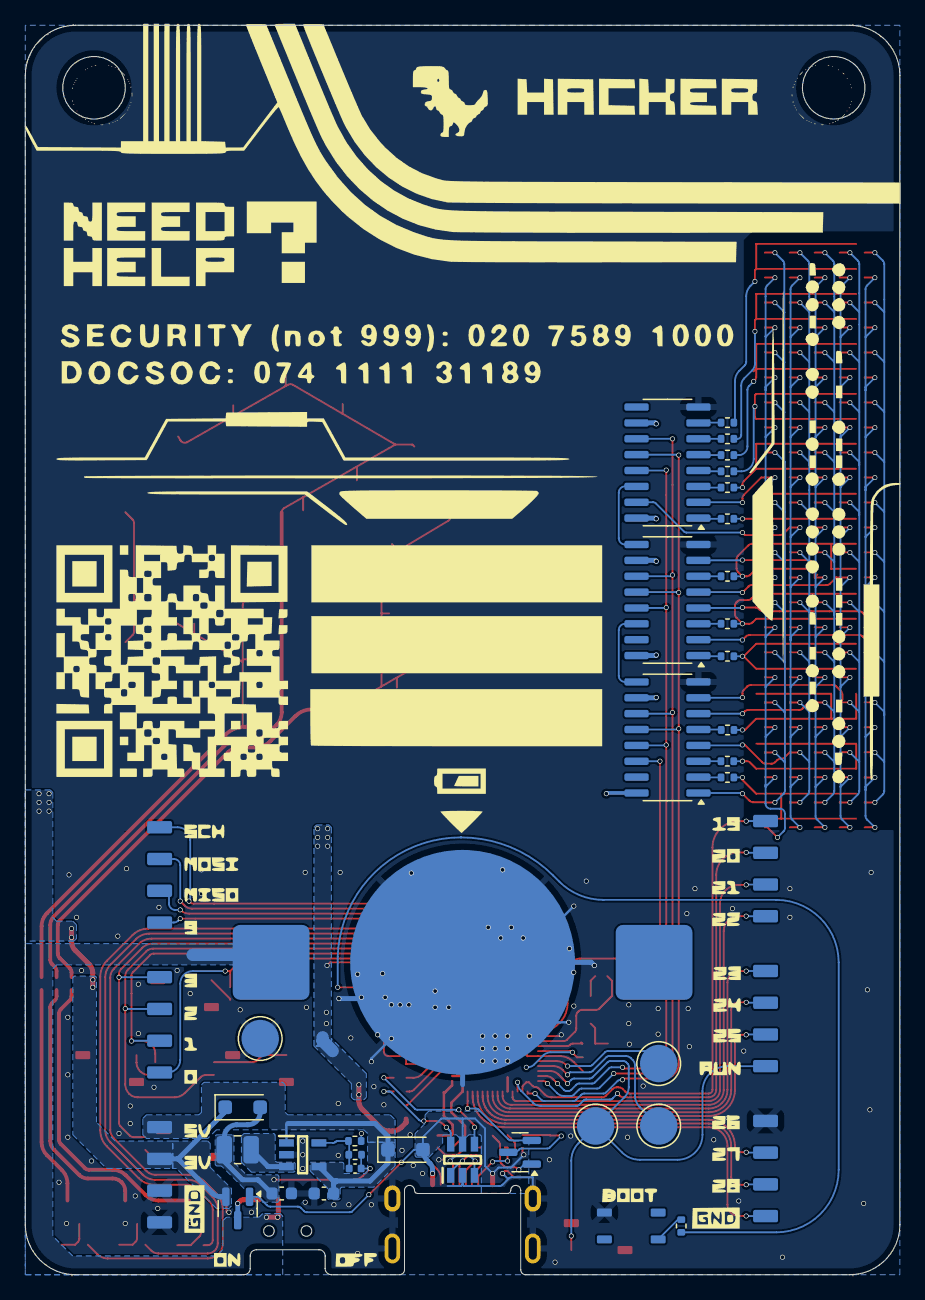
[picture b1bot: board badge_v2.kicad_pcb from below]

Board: 2 copper layers, 70.0 x 100.0 mm, 231 parts (40 on the bottom side), 108 nets.

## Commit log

2025-01-31 Added arduino submodule
2025-01-31 Removed submodule
2025-01-31 Re-added submodule
2025-01-31 Added hardware files and firmware binary
2025-02-01 Added content
2025-02-01 Updated README and added default firmware.
2025-02-01 Added buttons to pin table
